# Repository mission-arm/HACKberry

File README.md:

We are going to update HACKberry bionic arm to the next level. https://github.com/mission-arm/HACKberry

We want to use most of the 3D parts but redefining the sensoric, electronics and software used in the original project

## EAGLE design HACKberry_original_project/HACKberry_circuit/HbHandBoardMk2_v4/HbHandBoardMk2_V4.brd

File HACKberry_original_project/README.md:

For readers of *Fusion 360 Masters*

To get a STEP file in the old version, click [here](https://github.com/mission-arm/HACKberry/blob/dd13167829a51656212a1f741b30ab4311854cc5/HACKberry-hardware/3D/HACKberry_v1.stp).

Fusion 360 Masters をご購入頂いた方へ

対応するバージョンのSTEPファイルは[ここ](https://github.com/mission-arm/HACKberry/blob/dd13167829a51656212a1f741b30ab4311854cc5/HACKberry-hardware/3D/HACKberry_v1.stp)からダウンロードしてください。

# HACKberry
HACKberry is a practical model for daily use created through the cooperation of actual users.
Hackberries, which are a species of trees included in the elm family, grow many branches.
Our goal is to develop an artificial arm that would become the platform upon which developers and artificial arm users from all over the world are able to build as they wish.
The name represents our vision to “hack” at problems, grow branches of joy that reach out to users and enable their ideas and efforts to bear fruit (“berries”).

"HACKberry" provides dual licenses system for Users: one is for non-profit use under this Policy, and the other is for exceptional use (including commercial use).

Contents uploaded to the Exiii forum or GitHub may not only be used for development of HACKberry and may not be limited to just Creative Commons Licenses, and may be distributed by Exiii under a proprietary closed license, regardless of whether the content is program code, bug reports, opinions, ideas, etc. and regardless of the circumstances in which it was uploaded or whether it will be used for profit or not.

# HACKberry Open Source Project Policy

This policy (“Policy”) of “HACKberry Open Source Project” ( “Project”) sets forth the scope and the terms and conditions of the provision of the source codes and data etc. regarding “HACKberry” by Exiii Inc. (“Company”).

## 1. Purpose
1.1. The purpose of the Project is for the Company to release the source codes and data etc. and license the Company’s invention to all users of the Project (“Users”) in accordance with the Policy to promote the research development and spreading of artificial arms.

1.2. Users shall not use the source codes and data or the inventions released or licensed under the Policy for any of the following purposes:
1.2.1. military purpose.
1.2.2. purpose against public order or morality.
1.2.3. purpose of defaming or damaging the credit of the Company or HACKberry; and
1.2.4. any other purposes that the Company determines falls or is likely to fall under any of the above section 1.2.1. to 1.2.3.

## 2. Source Codes for Software
The source codes for the software of HACKberry are released under the following licenses.

Please inquire to the following contact to use the source code under exceptional conditions(commercial use, etc.).
[info@exiii.jp](mailto:info@exiii.jp)

|source codes|licenses|
|:-:|:-:|
|2.1. Arduino Sketch (the source code for Arduino Micro built into the artificial arms)|[GNU General Public License version 3](http://www.gnu.org/licenses/quick-guide-gplv3.en.html)|

## 3. Data for Hardware
The data for the hardwares of HACKberry is released under the following licenses.

Please inquire to the following contact to use the data under exceptional conditions(commercial use, etc.).
[info@exiii.jp](mailto:info@exiii.jp)

|Data|licenses|
|:-:|:-:|
|3.1. 3D data (the configuration data for each of the parts used in the artificial arms)|[Creative Commons License BY-NC-SA 4.0 International](https://creativecommons.org/licenses/by-nc-sa/4.0/)|
|3.2. Hand substrates data (the data for circuit substrates connecting microcontroller boards, motors, sensors and batteries)|[Creative Commons License BY-NC-SA 4.0 International](https://creativecommons.org/licenses/by-nc-sa/4.0/)|
|3.3. Sensor substrates data (the data for circuit substrates used to fix reflection type photosensors that detect ridges in muscle tissue)|[Creative Commons License BY-NC-SA 4.0 International](https://creativecommons.org/licenses/by-nc-sa/4.0/)|
|3.4. Battery substrates data (the data for circuit substrates built into battery boxes)|[Creative Commons License BY-NC-SA 4.0 International](https://creativecommons.org/licenses/by-nc-sa/4.0/)|

## 4. Patents
4.1. The Company grants Users a free-of-charge, non-exclusive, non-transferable and non-sub-licensable license(without any restriction of territory or time) to use the Company’s inventions (including registered patent inventions and pending patent inventions) provided that (i)such usage is necessary for Users to make artificial arms by using the source codes and the data in accordance with the licenses provided under sections 2 and 3 and (ii) such usage is not in violation of section 1.2.

4.2. The inventions referred to in the preceding section 4.1. includes the invention regarding the joint mechanism that enables artificial arms to operate similarly to human arms with a simple conformation.Presently, the invention  is patent pending, however, the Company will update the details of the invention through appropriate methods (including revision of the Policy, notification on the forum on this website and etc.) according to the development in the patent application.

## 5. Trademark and Other Contents
5.1. The following trademark is registered.
Trademark: exiii
Registration number: 5786270

5.2. The following trademark is under procedure of application.
Trademark: HACKberry
Application number: 2016-042844, 2016-042845

5.3. The “Intellectual Property Rights” (hereinafter used to refer to any rights already owned or to obtain or apply for registration of such rights) which includes copyright (including the rights specified in articles 27, 28 and other articles of the Japanese Copyright Act; the same apply hereinafter), patent rights, utility model rights, design rights, trademark rights, and other intellectual  property rights in and to the trademarks and other contents of the Company are owned by the Company unless the Policy stipulates otherwise.

5.4. On the basis of this Policy, in the case when users publicly released source code or data that is copyrighted under copyright law and committed or uploaded to GitHub or our forum (http://exiii-hackberry.com/forums/), their copyrights shall be transferred to our Company at the time it is committed.

5.5. Users may not use the trademarks and other contents in any way without prior written permission by the Company.

5.6. To obtain the permission stipulated the preceding section 5.3., please contact the below Email address.
[info@exiii.jp](mailto:info@exiii.jp)

## 6. Superiority of the individual Licenses
In the event of discrepancy between the provisions of this Policy and the provisions of the licenses regarding the source codes and data provided under sections 2 and 3 of this Policy, the provisions of the licenses regarding the source codes and data provided under sections 2 and 3 shall prevail unless provided otherwise.

## 7. The Company’s Exemption of Liability
7.1. The Company shall not explicitly or implicitly guarantee that this website itself, the source codes and data provided on this website, and the licenses quoted in the Policy are free from de facto or legal flaws (including flaws relating to safety, reliability, accuracy, completion, validity, compatibility with certain purposes, security, as well as errors, bugs, and infringement of rights). The Company shall have no obligation to provide services regarding HACKberry free of such defects to  Users.

7.2. The Company shall not in any way be responsible for any disputes or damages whatsoever arising in relation to the usage of the source codes and data provided by the Company or the interpretation and application of the Policy among Users or between Users and third parties.

7.3. The Company shall not provide any guarantee that the source codes and data will constantly be available on this website at any time. The Company shall not in any way be responsible for any damages caused to Users or third parties that arises from a situation where the Company cannot provide the source codes and data irrespectively of the cause of such situation such as maintenance of this website.

## 8. Modification of the provision and contents etc.
8.1. The Company may modify the contents or methods of provision of the source codes and data, the content of the license to use the Company’s inventions, or terminate the provision or the license (hereinafter referred to as the “Modifications.”)  when the Company deems necessary, without providing prior notice to Users.

8.2. The Company shall not be responsible for any disputes between Users and third parties or damages to Users or third parties arising in relation to the Modifications.

## 9. Modification of the Policy
9.1. The Company may modify the Policy when the Company deems necessary, without providing prior notice to Users.

9.2. Users shall be deemed to have granted valid and irrevocable consent to the modified Policy by continuing to download or use the source codes and data, or use the Company’s inventions. However, such modifications shall not affect the contents of the licenses applicable to the source codes and data that are downloaded by Users prior to the modification of the Policy in accordance with the Policy prior to the modification of the Policy.

## 10. Governing Law and Jurisdiction
10.1. Where the Company has provided Users with a translation of the Japanese language version of the Policy (“Japanese Version”), the Japanese Version and a translation will govern the relationship between Users and the Company. In the event of a contradiction between Japanese Version and a translation, the provisions in the Japanese Version shall take precedence over any other translation. The Policy shall be governed by the laws of Japan.

10.2. Any disputes that arise from the Policy or are related to the Policy will be governed primarily under the exclusive jurisdiction of the Tokyo District Court or the Tokyo Summary Court.

exiii Inc.
Prescribed on May 25th, 2015
Updated on July 20th, 2015
Updated on February 2nd, 2016
Updated on June 10th, 2016

# HACKberry
HACKberryは日常的に使えるようユーザーの声を多く取り入れた実用的な義手です。
Hackberryとはニレ科の非常に枝を多くつける樹木です。世界中の開発者や義手ユーザーが思い思いの形に作り上げられるプラットフォームになるような義手を目指します。
「改良（HACK）することで楽しみ方の枝葉が広がりユーザーの手に届き実(berry）を結ぶ」という思いを込めています。
「HACKberry」は、本規約に基づく非営利利用の場合とそれ以外の場合（営利利用など）を区別してライセンスを用意しています（デュアルライセンス方式を採用）。
exiiiのフォーラムとGitHubにアップロードされた内容は、プログラムコードに限らず、不具合報告、意見、アイディア、その他内容の如何や、営利または非営利利用を問わず、「HACKberry」の開発に利用され、Creative Commonsライセンスのみならず、exiii株式会社が独自に設定するクローズドソースライセンスの下で頒布されることがあります。

# HACKberry Open Source Project Policy(Japanese)

イクシー株式会社（以下「当社」といいます。）は、本ポリシーにおいて、「HACKberry」に関するソースコードおよびデータ等の公開（以下「本プロジェクト」といいます。）の内容およびその利用条件等について定めます。

## 1. 目的
1.1. 本プロジェクトの目的は、当社が本プロジェクトの一切の利用者（以下「ユーザー」といいます。）に対し、本ポリシーに基づいてソースコードおよびデータを公開し、当社の発明について利用許諾をすることで、義手の研究開発および普及を促進することにあります。

1.2. 本ポリシーに基づいて公開されたソースコードおよびデータ、または本ポリシーに基づいて利用許諾された発明について、以下の各号に規定する目的での使用を禁止します。
1.2.1. 軍事目的での使用
1.2.2. 公序良俗に反する目的での使用
1.2.3. 当社またはHACKberryの名誉または信用毀損する目的での使用
1.2.4. 当社が上記各号に該当するおそれがあると判断する目的による使用

## 2. ソフトウェアのソースコード
HACKberryに関するソフトウェアのソースコードは、以下のライセンスに基づき公開されます。各ライセンスとは異なる条件（商用利用等）でソースコードの利用を希望する場合は、以下のアドレスまでご連絡ください。
[info@exiii.jp](mailto:info@exiii.jp)

|ソースコード|ライセンス|
|:-:|:-:|
|2.1. Arduinoスケッチ（義手に内蔵したArduino Microに書き込むためのソースコードを意味します。）|[GNU General Public License version 3](http://www.gnu.org/licenses/quick-guide-gplv3.en.html)|

## 3. ハードウェアに関するデータ
HACKberryに関するハードウェアに関する各データは、以下の各ライセンスまたは条件に基づき公開されます。 各ライセンスとは異なる条件（商用利用等）でデータの利用を希望する場合は、以下のアドレスまでご連絡ください。  [info@exiii.jp](mailto:info@exiii.jp)

|データ|ライセンス|
|:-:|:-:|
|3.1. 3Dデータ（義手に使う各部品の形状データを意味します。）|[Creative Commons License BY-NC-SA 4.0 International](https://creativecommons.org/licenses/by-nc-sa/4.0/)|
|3.2. ハンド基板データ（マイコン、モーター、センサおよび電池を繋ぐための回路基板を意味します。）|[Creative Commons License BY-NC-SA 4.0 International](https://creativecommons.org/licenses/by-nc-sa/4.0/)|
|3.3. センサ基板データ（筋肉の隆起を検出するための反射型光センサ（フォトリフレクタ）を取り付けるための回路基板を意味します。）|[Creative Commons License BY-NC-SA 4.0 International](https://creativecommons.org/licenses/by-nc-sa/4.0/)|
|3.4. 電池基板データ（電池ボックスに内蔵する回路基板を意味します。）|[Creative Commons License BY-NC-SA 4.0 International](https://creativecommons.org/licenses/by-nc-sa/4.0/)|

## 4. 特許
4.1. 当社は、ユーザーに対し、2.および3.に定めたライセンスに基づいてソースコードまたはデータを利用して義手を制作するに当たって必要な範囲であってかつ1.2.に違反しない場合に限り、当社が特許出願中または特許登録済みの発明を実施することを、無償で、地域または期間の限定なく、非独占的に許諾（再許諾は除きます。）します。

4.2. 4.1.に定める発明は、関節機構に関するものであって、簡単な構造で人間の手の動作に近い動作を実現可能とするものです。現在特許出願中ですが、出願手続の進展に応じて、発明の特定に関する情報を本ポリシーまたはフォーラム等において適切な方法により告知します。

## 5. 商標等およびコンテンツ
5.1. 以下の商標は、当社が日本において登録済の商標です。
商標：exiii
登録番号：5786270

5.2. 以下の商標は、当社が日本において出願中の商標です。
商標：HACKberry
登録番号：2016-042844, 2016-042845

5.3. 本ポリシーに特に定めがない限り、exiiiに関する商標等およびコンテンツについて、著作権（著作権法第27条および第28条の権利その他の権利を含みます。以下、同様とします。）、特許権、実用新案権、意匠権、商標権等の知的財産権（それらの権利を取得し、またはそれらの権利につき登録等を出願する権利も含むものとします。以下、総称して「知的財産権」といいます。）その他一切の権利は、当社に帰属します。

5.4. ユーザーが本ポリシーに基づいて公開されたソースコードおよびデータに関し、GitHubまたはフォーラム（http://exiii-hackberry.com/forums/ ）上でコミットまたはアップロードした場合、その内容が著作権法上の著作物であるときには、コミットと同時に、ユーザーの著作権は当社に移転します。また、この場合、ユーザーは、当社または当社が許諾する第三者に対し、著作者人格権を行使しないものとします。

5.5. 商標等およびコンテンツは、当社の事前の書面による許諾を得ない限り、いかなる利用もしてはなりません。

5.6. 商標等またはコンテンツの利用を希望する場合は、以下のアドレスまでご連絡ください。
[info@exiii.jp](mailto:info@exiii.jp)

## 6. 個別のライセンスの優先
第2項または第3項に規定するソースコードまたはデータに付与されたライセンスに規定する事項のなかで、本ポリシーと第2項または第3項に規定するソースコードまたはデータに付与されたライセンスとの間に、同一の事項について異なる内容がある場合には、特段の定めがないかぎり、各ライセンスの内容を優先して適用する。

## 7. 免責
7.1. 当社は、本ウェブサイト、本ウェブサイトで提供されるソースコードおよびデータならびに本ポリシーに掲げる各ライセンスに事実上または法律上の瑕疵（安全性、信頼性、正確性、完全性、有効性、特定の目的への適合性、セキュリティなどに関する欠陥、エラーやバグ、権利侵害などを含みます。）がないことを明示的にも黙示的にも保証しておりません。当社は、ユーザーに対して、かかる瑕疵を除去してHACKberryに関するサービスを提供する義務を負いません。

7.2. 当社は、当社が提供するソースコードおよびデータの使用または本ポリシーに定める各ライセンスの解釈適用に関連してユーザー間またはユーザーと第三者との間で生じた、いかなる形態での紛争またはあらゆる損害について一切の責任を負いません。

7.3. 当社は、本ウェブサイトにおいてソースコードおよびデータが常に提供されることを保証しません。当社は、本ウェブサイトのシステムの保守点検といった理由をとわず、本ウェブサイトにおいてソースコードおよびデータが提供できない事態が発生したことによってユーザーまたは第三者に生じるあらゆる損害について一切の責任を負いません。

## 8. 提供方法および内容の変更
8.1. 当社は、ユーザーに対してあらかじめ通知することなく、いつでも本ポリシーに定めるソースコードもしくはデータの提供方法もしくは提供内容または発明の利用許諾の内容を変更し、または提供もしくは利用許諾を中止すること（以下「変更等」といいます。）ができます。

8.2. 当社は、前項の変更等に関連して、ユーザーまたは第三者に生じるあらゆる紛争または損害について一切の責任を負いません。

## 9. 本ポリシーの変更
9.1. 当社は、ユーザーに対してあらかじめ通知することなく、いつでも本ポリシーの内容を変更することができます。

9.2. ユーザーは、本ポリシーの変更があった後、当社が提供するソースコードもしくはデータの取得もしくは利用を継続することによって、または当社の発明の利用を継続することによって、変更後の本ポリシーについて有効かつ取消不能な同意をしたものとみなします。ただし、本ポリシー変更前にユーザーが変更前のポリシーに基づいて取得したソースコードまたはデータに適用されるライセンスの内容はこの限りではありません。

## 10. 準拠法、裁判管轄
10.1. 本ポリシーは、日本語を正文とし、準拠法は日本法とします。

10.2. 本ポリシーに起因し、または関連する一切の紛争については、訴額に応じて、東京地方裁判所または東京簡易裁判所を第一審の専属的合意管轄裁判所とします。

イクシー株式会社
2015年5月25日制定
2015年7月20日改訂
2016年2月2日改訂
2016年6月10日改訂

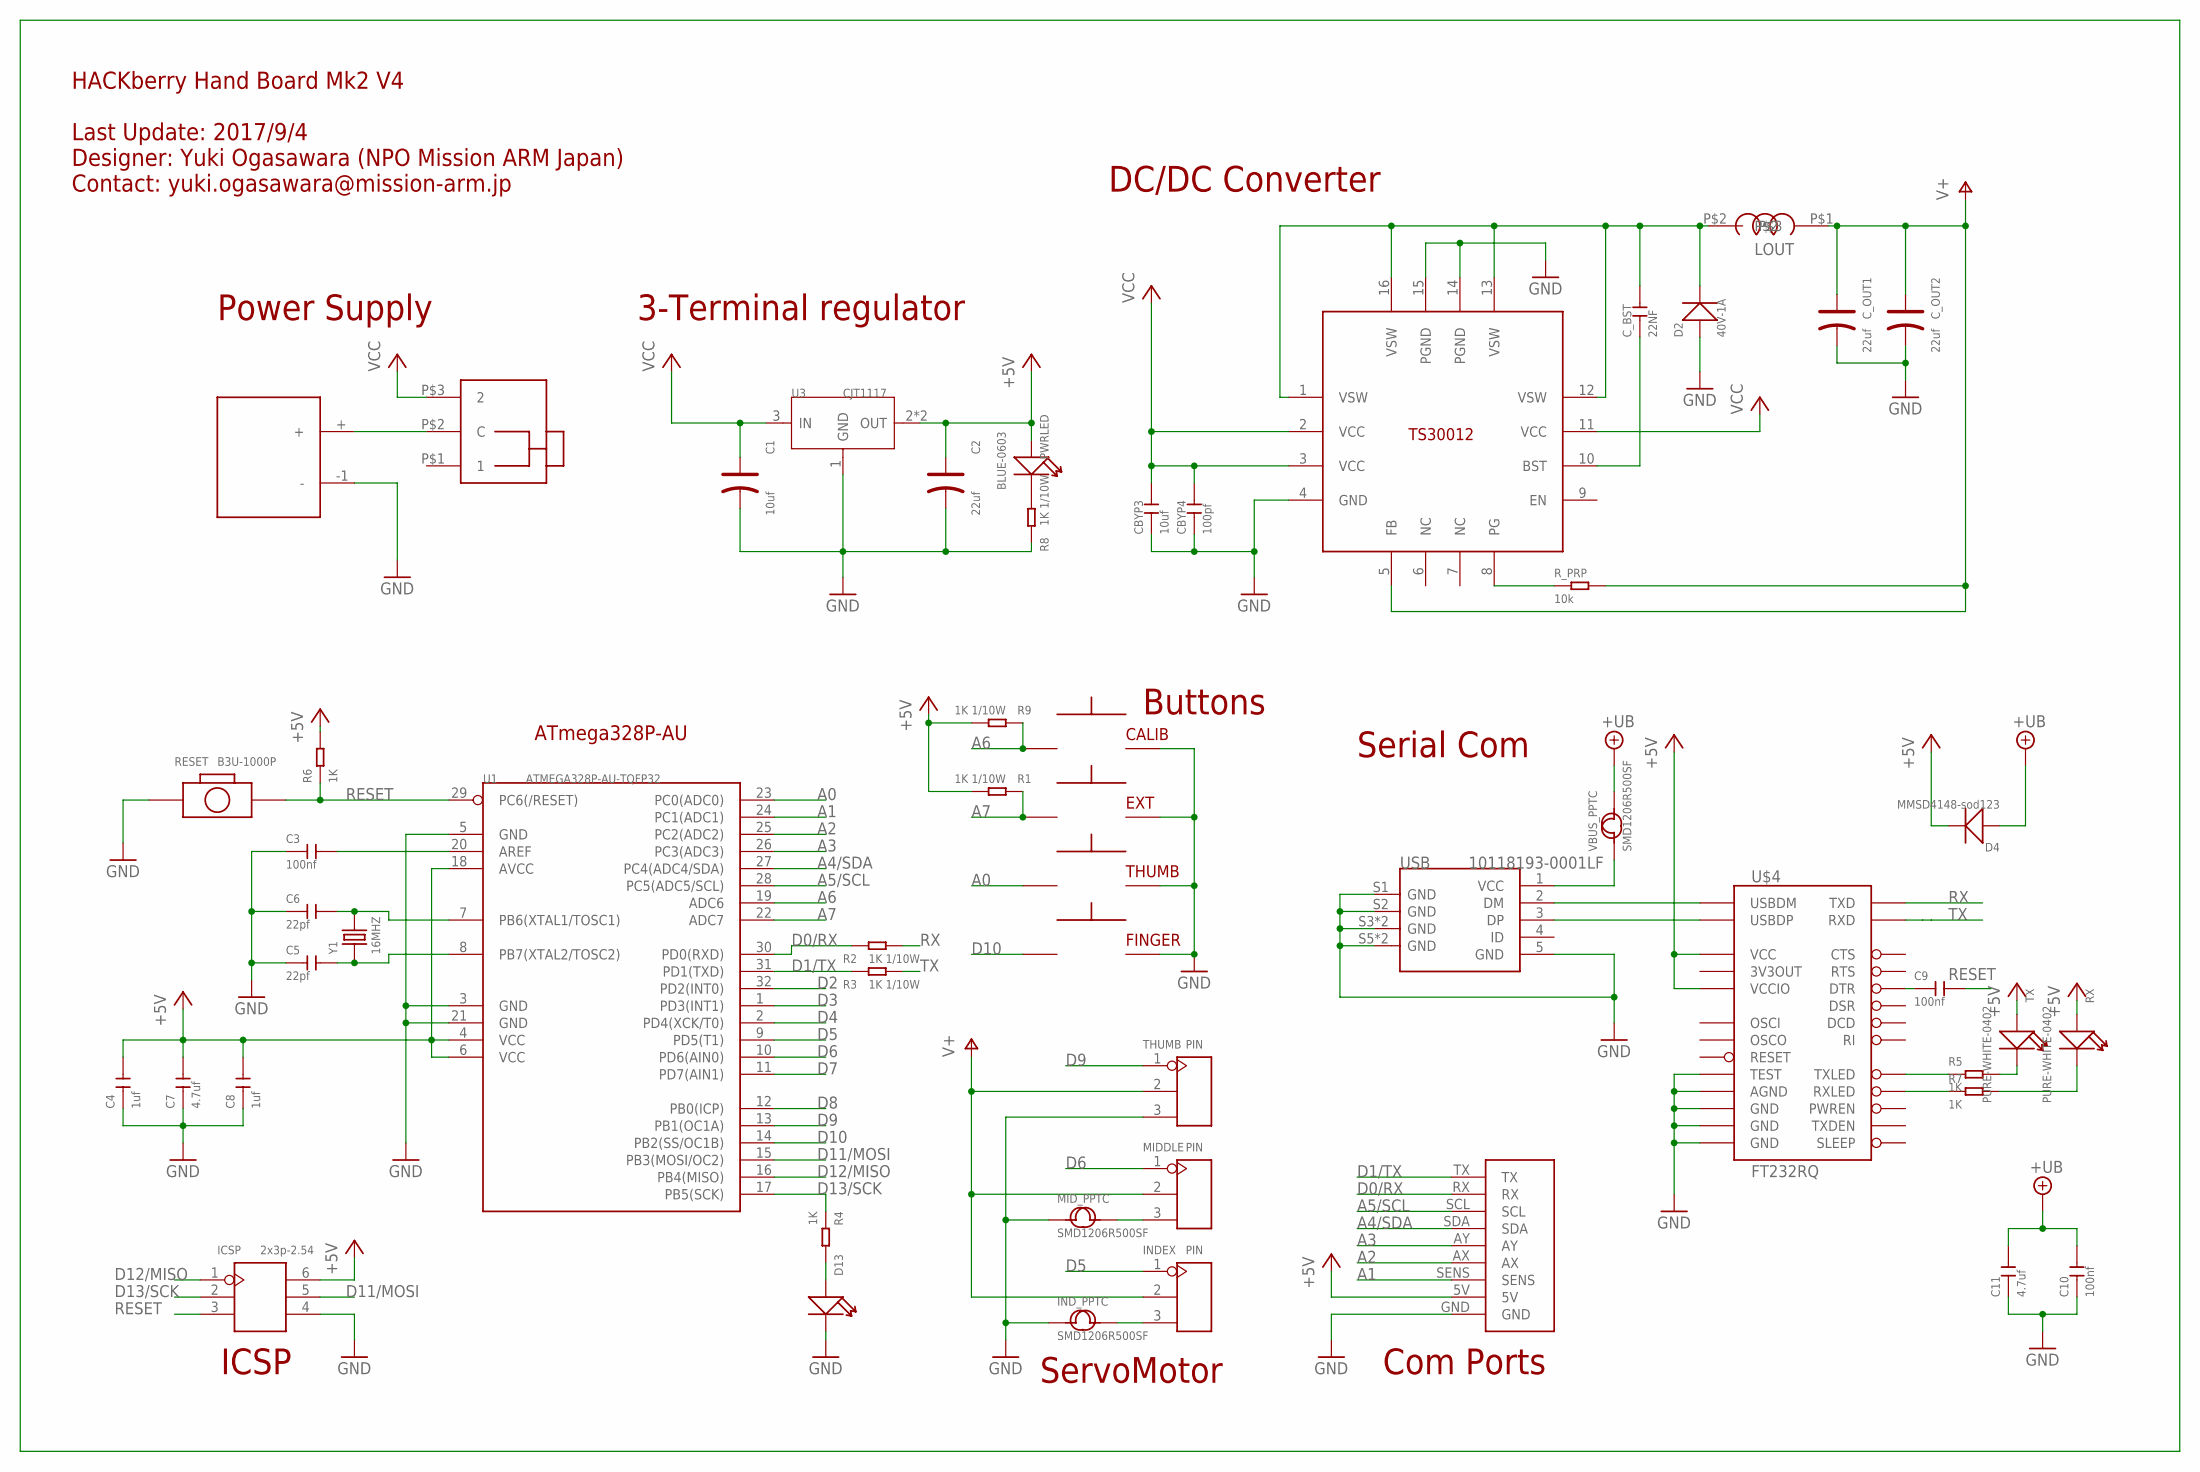
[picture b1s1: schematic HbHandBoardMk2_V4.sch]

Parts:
C1: 10uf; AVX-A
C2: 22uf; AVX-A
C3, C9, C10: 100nf; C0402
C4, C8: 1uf; C0402
C5, C6: 22pf; C0402
C7, C11: 4.7uf; C0603
CALIB: SKRGAQD010
CBYP3: 10uf; C0805
CBYP4: 100pf; C0402
C_BST: 22NF; C0402
C_OUT1, C_OUT2: 22uf; AVX-B
D2: 40V-1A; DO-214AC
D4: MMSD4148-sod123; SOD-123
D13: SMD-LED-CLEAR-GREEN(0805); LED-0805
EXT: SKRGAQD010
FINGER: SKRGAQD010
ICSP: 2x3p-2.54; H2X3-2.54
INDEX: PIN; H3-2.54
IND_PPTC: SMD1206R500SF; F1206
LOUT: SPM3015T-4R7M-LR
MIDDLE: PIN; H3-2.54
MID_PPTC: SMD1206R500SF; F1206
PWRLED: BLUE-0603; LED-0603
PWR_SW: SS12SDP2
R1, R2, R3, R8, R9: 1K 1/10W; R0603
R4: 1K; R0805
R5, R6, R7: 1K; R0402
RESET: B3U-1000P; SW2-SMD-3.0X2.5X1.2+0.4MM
RX: PURE-WHITE-0402; LED-0402
R_PRP: 10k; R0402
THUMB: PIN; H3-2.54
THUMB_BUTTON: SKRGAQD010
TX: PURE-WHITE-0402; LED-0402
U1: ATMEGA328P-AU-TQFP32; TQFP32-0.8-7X7MM
U3: CJT1117; SOT-223
U$1: 9PADS
U$3: DCJACK; DCJ3P-14.2X11.0X9.0MM
U$4: FT232RQ; QFN-32
U$6: TS30012; VQFN16
USB: 10118193-0001LF; MICRO-USB5+6P-SMD-0.65-B
VBUS_PPTC: SMD1206R500SF; F1206
Y1: 16MHZ; X2-SMD-5.0X3.2X1.3MM

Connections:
+5V: C2.+, C4.2, C7.2, C8.2, D4.-, ICSP.6, PWRLED.+, R1.2, R6.2, R9.2, RX.+, TX.+, U1.4 (VCC), U1.6 (VCC), U1.18 (AVCC), U3.2 (OUT), U3.TER (OUT), U$1.5V, U$4.1 (VCCIO), U$4.19 (VCC)
+UB: C10.2, C11.2, D4.+, VBUS_PPTC.2
A0: THUMB_BUTTON.P$1 (1), U1.23 (PC0(ADC0))
A1: U1.24 (PC1(ADC1)), U$1.SENS
A2: U1.25 (PC2(ADC2)), U$1.AX
A3: U1.26 (PC3(ADC3)), U$1.AY
A4/SDA: U1.27 (PC4(ADC4/SDA)), U$1.SDA
A5/SCL: U1.28 (PC5(ADC5/SCL)), U$1.SCL
A6: CALIB.P$1 (1), R9.1, U1.19 (ADC6)
A7: EXT.P$1 (1), R1.1, U1.22 (ADC7)
D0/RX: R2.1, U1.30 (PD0(RXD)), U$1.RX
D1/TX: R3.1, U1.31 (PD1(TXD)), U$1.TX
D2: U1.32 (PD2(INT0))
D3: U1.1 (PD3(INT1))
D4: U1.2 (PD4(XCK/T0))
D5: INDEX.1, U1.9 (PD5(T1))
D6: MIDDLE.1, U1.10 (PD6(AIN0))
D7: U1.11 (PD7(AIN1))
D8: U1.12 (PB0(ICP))
D9: THUMB.1, U1.13 (PB1(OC1A))
D10: FINGER.P$1 (1), U1.14 (PB2(SS/OC1B))
D11/MOSI: ICSP.5, U1.15 (PB3(MOSI/OC2))
D12/MISO: ICSP.1, U1.16 (PB4(MISO))
D13/SCK: ICSP.2, R4.1, U1.17 (PB5(SCK))
GND: C1.-, C2.-, C3.1, C4.1, C5.1, C6.1, C7.1, C8.1, C10.1, C11.1, CALIB.P$2 (2), CBYP3.1, CBYP4.1, C_OUT1.-, C_OUT2.-, D2.1 (+), D13.-, EXT.P$2 (2), FINGER.P$2 (2), ICSP.4, IND_PPTC.1, MID_PPTC.1, R8.1, RESET.1, THUMB.3, THUMB_BUTTON.P$2 (2), U1.3 (GND), U1.5 (GND), U1.21 (GND), U3.1 (GND), U$1.GND, U$3.-1 (-), U$4.4 (GND), U$4.17 (GND), U$4.20 (GND), U$4.24 (AGND), U$4.26 (TEST), U$6.4 (GND), U$6.14 (PGND), U$6.15 (PGND), USB.5 (GND), USB.S1 (GND), USB.S2 (GND), USB.S3 (GND), USB.S4 (GND), USB.S5 (GND), USB.S6 (GND)
unnamed: PWRLED.-, R8.2
unnamed: C5.2, U1.8 (PB7(XTAL2/TOSC2)), Y1.1
unnamed: C6.2, U1.7 (PB6(XTAL1/TOSC1)), Y1.2
unnamed: D13.+, R4.2
unnamed: U$4.15 (USBDM), USB.2 (DM)
unnamed: C3.2, U1.20 (AREF)
unnamed: U$4.14 (USBDP), USB.3 (DP)
unnamed: C_BST.2, D2.2 (-), LOUT.P$2, U$6.1 (VSW), U$6.12 (VSW), U$6.13 (VSW), U$6.16 (VSW)
unnamed: PWR_SW.P$2 (C), U$3.+
unnamed: C_BST.1, U$6.10 (BST)
unnamed: INDEX.3, IND_PPTC.2
unnamed: MIDDLE.3, MID_PPTC.2
unnamed: R_PRP.1, U$6.8 (PG)
unnamed: C9.1, U$4.31 (DTR)
unnamed: USB.1 (VCC), VBUS_PPTC.1
unnamed: R5.1, U$4.22 (TXLED)
unnamed: R7.1, U$4.21 (RXLED)
unnamed: R5.2, TX.-
unnamed: R7.2, RX.-
RESET: C9.2, ICSP.3, R6.1, RESET.2, U1.29 (PC6(/RESET))
RX: R2.2, U$4.30 (TXD)
TX: R3.2, U$4.2 (RXD)
V+: C_OUT1.+, C_OUT2.+, INDEX.2, LOUT.P$1, MIDDLE.2, R_PRP.2, THUMB.2, U$6.5 (FB)
VCC: C1.+, CBYP3.2, CBYP4.2, PWR_SW.P$3 (2), U3.3 (IN), U$6.2 (VCC), U$6.3 (VCC), U$6.11 (VCC)

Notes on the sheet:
ATmega328P-AU
Power Supply
ServoMotor
3-Terminal regulator
Buttons
Com Ports
DC/DC Converter
HACKberry Hand Board Mk2 V4 Last Update: 2017/9/4 Designer: Yuki Ogasawara (NPO Mission ARM Japan) Contact: yuki.ogasawara@mission-arm.jp
ICSP
Serial Com
FINGER
THUMB
CALIB
EXT

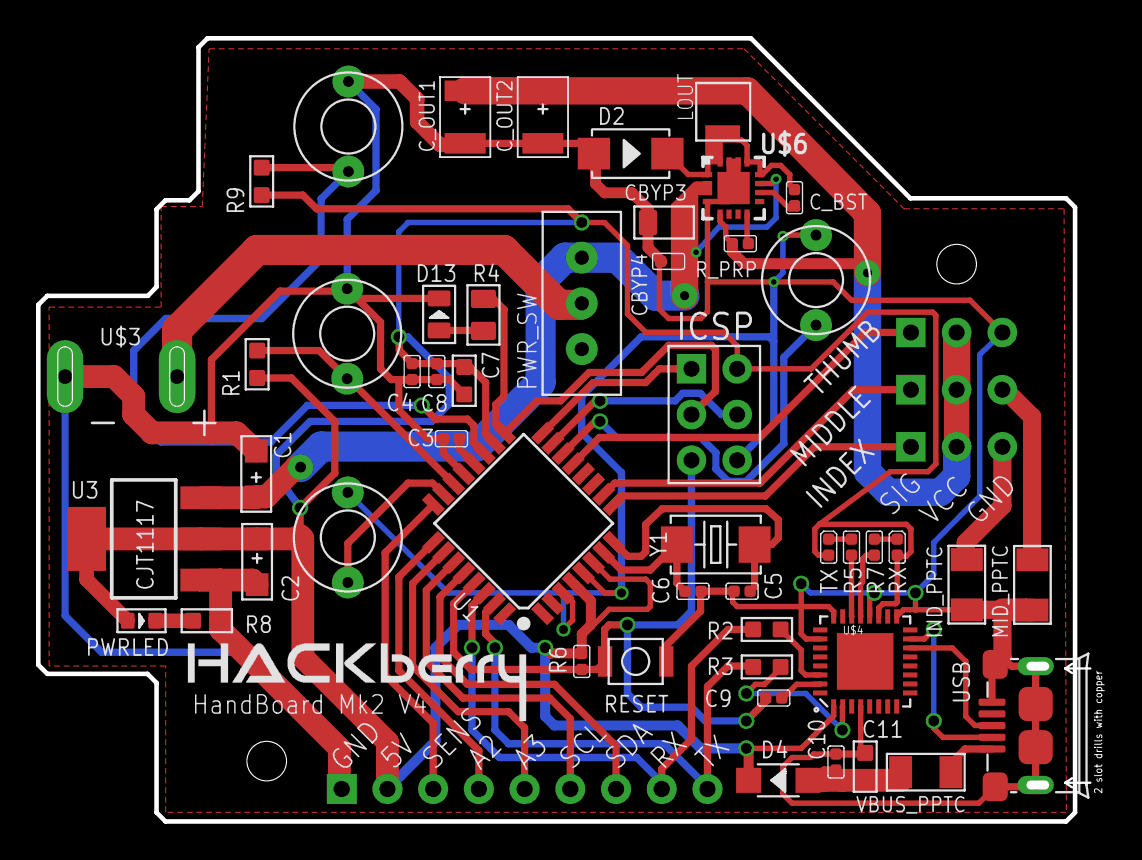
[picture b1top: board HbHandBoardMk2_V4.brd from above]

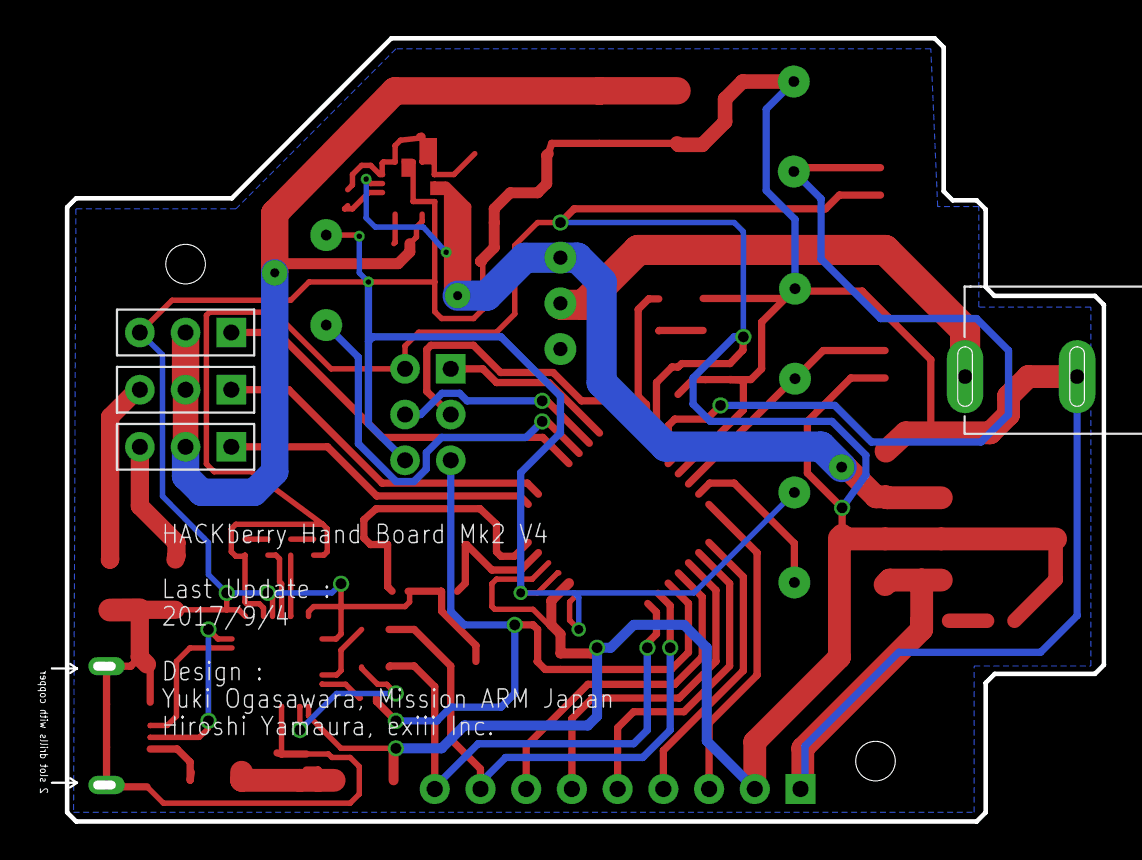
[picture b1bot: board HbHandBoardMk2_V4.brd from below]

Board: 2 copper layers, 58.5 x 43.5 mm, 54 parts (4 on the bottom side), 44 nets.

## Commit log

2015-05-17 first commit
    first commit
2015-05-18 test
    comment test
2015-05-20 hardwareTest1
    hardwareTest1
2015-05-20 test1
    test2
2015-05-20 uploadTest
2015-05-20 delete
2015-05-21 test
2015-05-21 test2
2015-05-21 refactored
2015-05-22 upload
2015-05-23 rivice of the schematic
    add the parts name of slide switch
2015-05-23 rivice of the README.md
2015-05-23 bug fix
2015-05-23 add
    upload the battery board data and sensor board data
2015-05-23 rivision of the README.md
2015-05-23 rivision of the policy
2015-05-25 Fixed minor formatting issues
2015-05-27 Fixed incorrect appearance in schematic
2015-05-29 Revert "Fixed incorrect appearance in schematic"
    This reverts commit 3b6817b660281c2eda156baa4225a43203330258.
2015-05-29 modify
2015-05-29 Revert "Revert "Fixed incorrect appearance in schematic""
    This reverts commit 5cdc5c46337e107bca08166c1673e08221bf1df3.
2015-05-29 Revert "modify"
    This reverts commit 7cc21e78040ca20a5a75b3f63a87baaadaba0b3a.
2015-05-29 Uploaded the Inventor data
2015-06-02 Deleted Files
2015-06-03 Upload STL files
2015-06-03 Upload BOM
2015-06-03 Modify the problem of thin-wall
2015-06-05 Added flat screws
2015-06-05 Added flat screw
2015-06-05 Added tension spring
2015-06-07 Modified the schematic.
    Added the push switch.
2015-06-07 Updated the schematic
2015-06-10 Fixed an error of SensorBoard schematic
    resistance values were not correct.
2015-06-14 Added presentation files
2015-06-25 Proceeded detail design of the hand boad
2015-06-30 Added README.md
    Licenses about the sensor system.
2015-06-30 Fixed minor miswriting
2015-07-03 made the garber data of the HandBoard_v1
2015-07-03 made the garber data of HandBoard_v1
    this data is not tested yet. I will make PCB using this data on July 7.
2015-07-21 test
    test
2015-07-21 Fixed english descriptions
2015-07-22 Fixed file error
2015-07-22 Updated the garber data of HandBoard_v1
2015-07-23 Updated the BOM
    Added the sensor parts to BOM list.
2015-07-29 Fixed index finger's interference
2015-07-29 Updated STL data
2015-07-30 Fixed minor error.
2015-07-30 Deleted a wrong link
2015-08-01 Added the update date.
2015-08-03 Added the link to a substitution of small servo motor
    Emax ES08MD
2015-08-05 Updated the substitution link of the battery.
2015-08-05 Deleted unnecessary libraries.
2015-08-05 Uploaded the 3D data of new socket
2015-08-11 Added garber data of SensorBoard
2015-08-11 Fixed minor error
2015-08-13 Fixed the error of Arduino_micro foot print
2015-08-22 Upgraded the strength of index finger
2015-08-22 Fixed reference problem of libraries.
2015-08-23 Fixed minor errors
2015-08-23 Fixed minor erroes
2015-08-26 Upgraded the shaft stoppers
2015-08-26 Updated the 3D data.
2015-09-06 Added minor errors of BOM
2015-09-06 Fixed minor problem of 3D data
2015-09-07 Upgraded the wrist part
    The wrist part (HbPalmBase03) is modified so that it can be attached
    both HACKberry's socket and conventional body-powered prosthesis.
2015-09-08 Added the images of PCB
2015-09-11 Started designing HandBoard_v2
2015-09-16 Fixed the error of the screw length
2015-09-16 Added the STL files of new socket
2015-09-16 Modified the mechanism of thumb.
    Added the manual joint to thumb. It enables users to change hand posture
    from pinching to grasping.
2015-09-17 Upload the STL data of pcb boards
2015-09-17 Modified the mechanism of thumb. 02
2015-09-27 Changed the small servo and fixed minor errors.
    Changed ASV-15MG to ES08MD.
2015-10-07 Added the url for a spring store
2015-10-07 Added STL data for left hand
2015-10-07 Simplified the structure of BatteryDoor and Added some parts data for left hand.
2015-10-08 Added Arduino sketch for left hand
2015-11-03 Updated the HandBoard
    changed the voltage for sensor from 3.3[V] to 5.0[V].
    modified the garber data for milling.
2015-11-03 Added the STL data for ledt hand.
2015-11-03 Modified the structure of the Battery Unit.
2015-11-06 Updated assembly files
2015-11-06 Updated the 3D data
    -Enlarged the clearance gaps between parts
    -Standardized the screws
2015-11-12 Updated BOM
2015-11-18 Updated the link of steel ball
2015-11-26 Uploaded the PCB files for manufacturing
2015-12-02 organezed the STL folder
2015-12-11 Fixed minor URL error
2015-12-14 Updated STP file.
2015-12-18 Added SensorBoard_v1_1
2015-12-19 Updated thumb mechanism.
2015-12-23 Added polygon data of HACKberry
    Polygonised by Yuji Yoshikai + Hiroshi Ishikawa
    This work is part of Kota Nezu's project.
2015-12-23 Changed the configuration of battery case
2016-01-04 Added README.md
2016-01-05 Apdated STEP and Parasolid files
2016-01-26 Updated the PCB files for PCB manufacturing service.
2016-01-28 Updated 3D data
    Modified features so that the parts can be printed with less support
    materials.
2016-01-28 Updated the BOM
2016-01-30 Added missing STL files
2016-02-02 Updated the terms of use.
2016-02-11 左手用メインボードを設計完了
2016-02-11 Updated Assembly data
    STEP, Parasolid, IGES
2016-02-11 Fixed minor error of HbPalmBase03
2016-02-12 Deleted unnecessary files.
2016-02-16 Fixed minnor mistakes of 3D data.
2016-02-17 Updated Sensor system.
    Added a plate which covers the sensor.
2016-02-18 Change DC-jack to PJ-102A
2016-02-19 Updated the problem of assmebling.
2016-02-21 Updated the BOM
    Added 3001HB as a substitution for S03N.
2016-02-23 Solved the problem of the HbPalmBase weakness.
2016-02-25 Add BOM for 3D printing service
2016-02-25 Make 3D Print1 assembly.
2016-02-25 Make 3D Print2 and 3 assembly
2016-02-25 Make 3D print4~7 assembly
2016-02-25 Update list of WristU's parts on BOM for printing.
2016-02-25 update assembly for print6 & 7
2016-02-25 Make assembly of all parts for printing
2016-02-25 add Case of parts
2016-02-25 Change pitch of mesh on PrintingCase
2016-02-25 Update thumb assembly
    reinforce the thumb
2016-02-26 Update thumb 3D data
    Reinforce the thumb structure
2016-02-29 Update the thumb data for left hand.
2016-03-02 change initial position of thumb for assembling
2016-03-02 Update HandBoard garber data for left hand
2016-03-09 Fix assembling problem
2016-03-16 Reinforce battery hinge
2016-03-24 enlarge diameter of prepared holes
    from 1.6 or 1.7 mm to 1.8mm. It will make assembling easy.
2016-03-24 Update 3D data
2016-03-29 Add vercro band for sensor unit to BOM list
2016-03-30 Reverse the value of sensor
2016-04-07 Update the 3D data
2016-04-07 Update the BOM
    add audio cable. correct some mistakes.
2016-04-07 Update inventor files
2016-04-07 correct some mistakes in BOM
2016-04-07 fixe interference of the finger
2016-04-08 correct the number of screw
2016-04-17 divide MainFrame!01 into two parts
2016-05-03 devide HbMainFrameA01 into two pieces
2016-05-03 divided MainFrameA into two pieces.
2016-05-06 change the number of screw in BOM
2016-05-10 update HbShaftStopperB to correct version.
2016-06-03 trial and error
2016-06-06 change the arrangement of pins and the size of DC-DC converter and rewire all routes.
2016-06-06 change the voltage to sensor to 5V
2016-06-10 make assemble file for SLS printing
2016-06-11 Update terms of use
2016-06-12 Fix minor formatting issues.
2016-06-15 added drill for eyephone jack
    added polygon for GND on buttom layer
    made garbar data
2016-06-17 add poly switch to protect servo motor
2016-06-17 modified texts and add polygon on internal layers
2016-07-10 replace servo motor S03N with HD3001HB
2016-08-24 pr/12
2016-08-24 Fix minor errors
2016-08-24 Fix the positions of switches.
2016-09-05 Fix minor name error
2016-09-05 Make small dent in to avoid collision between HBarmMountBaseCover03.ipt and HBabductionLever02.
2016-09-08 Reinforce the thumb unit.
2016-10-16 yuki.ogasawara
    2016/10/16_小笠原プログラム変更
2016-11-09 Reinforce the thumb unit 02
2017-01-04 Program fix
    Correction of rotation direction of servo motor of index finger
2017-04-26 add .gitignore for hardware directory
2017-04-26 change .gitignore
2017-09-02 Create Questions and remarks
2017-09-21 upgrade hardware, circuits and software to mk2
2017-09-21 add STL and STEP data for SLS print
2017-09-28 Update and sort the BOM file
2017-10-22 Rename directories
2017-11-28 add graps mode and serial num out
2017-12-13 シリアルナンバーの出力ができない問題の修正
2018-02-20 ボードのバージョンによる分岐を追加 サーボのピンとセンサーのピンを後で変更するようにした
2018-02-20 mk2のボタン仕様に対応(pullupのないpinがある)
2018-03-05 fix some interference
2018-04-25 add an arduino sketch for HACKberry Mk2.
2018-04-30 fix some bugs about button reading
2018-05-16 add arduino software for EMG
2018-06-29 add Reverse Button
2018-06-29 fix local variable initialization in Hackberryv3.0.ino
2018-08-19 fix hyper link for DCDC converter
2018-08-19 fix some error for compile
2026-02-01 TODO added
2026-02-02 new documentation
2026-02-03 new doc for 3d models

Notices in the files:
HACKberry_original_project/README.md:
exiiiのフォーラムとGitHubにアップロードされた内容は、プログラムコードに限らず、不具合報告、意見、アイディア、その他内容の如何や、営利または非営利利用を問わず、「HACKberry」の開発に利用され、Creative Commonsライセンスのみならず、exiii株式会社が独自に設定するクローズドソースライセンスの下で頒布されることがあります。
2.1. Arduinoスケッチ（義手に内蔵したArduino Microに書き込むためのソースコードを意味します。）|[GNU General Public License version 3](http://www.gnu.org/licenses/quick-guide-gplv3.en.html)
3.1. 3Dデータ（義手に使う各部品の形状データを意味します。）|[Creative Commons License BY-NC-SA 4.0 International](https://creativecommons.org/licenses/by-nc-sa/4.0/)
